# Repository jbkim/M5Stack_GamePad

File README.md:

# M5Stack_GamePad
### M5Stack용 Gamepad
- I2C 디바이스로 동작함
- M5Stack의 I2C포트에 연결이 되어 조이스틱의 값 및  버튼입력 값을 받을 수 있다.
- M5Stack용 Joystck과 사용법이 같다. https://docs.m5stack.com/#/en/unit/joystick
- 차이점은
    - requestFrom 함수의 인자값을 3 대신 4로 입력한다.
    - 키 버튼의 맵핑은 
    ```cpp
        void loop() {
        // put your main code here, to run repeatedly:
        Wire.requestFrom(JOY_ADDR, 4);
        if (Wire.available()) {
            x_data = Wire.read();
            y_data = Wire.read();
            select_data = Wire.read(); // Joystick button
            btn_data = Wire.read();    // Keypad button: up, down, left, right
                
            sprintf(data, "x:%d y:%d button:%d\n", x_data, y_data, select_data);
            Serial.print(data);

            if (btn_data & UP) Serial.println("UP");
            if (btn_data & DOWN) Serial.println("DOWN");
            if (btn_data & LEFT) Serial.println("LEFT");
            if (btn_data & RIGHT) Serial.println("RIGHT");                
        }
        delay(200);
        }
    ```

- History
    - Version 1.0

    - Version 1.1
        - I2C 포트의 위치 변경
        - 홀 사이즈 변경
        - PCB 레이아웃 변경

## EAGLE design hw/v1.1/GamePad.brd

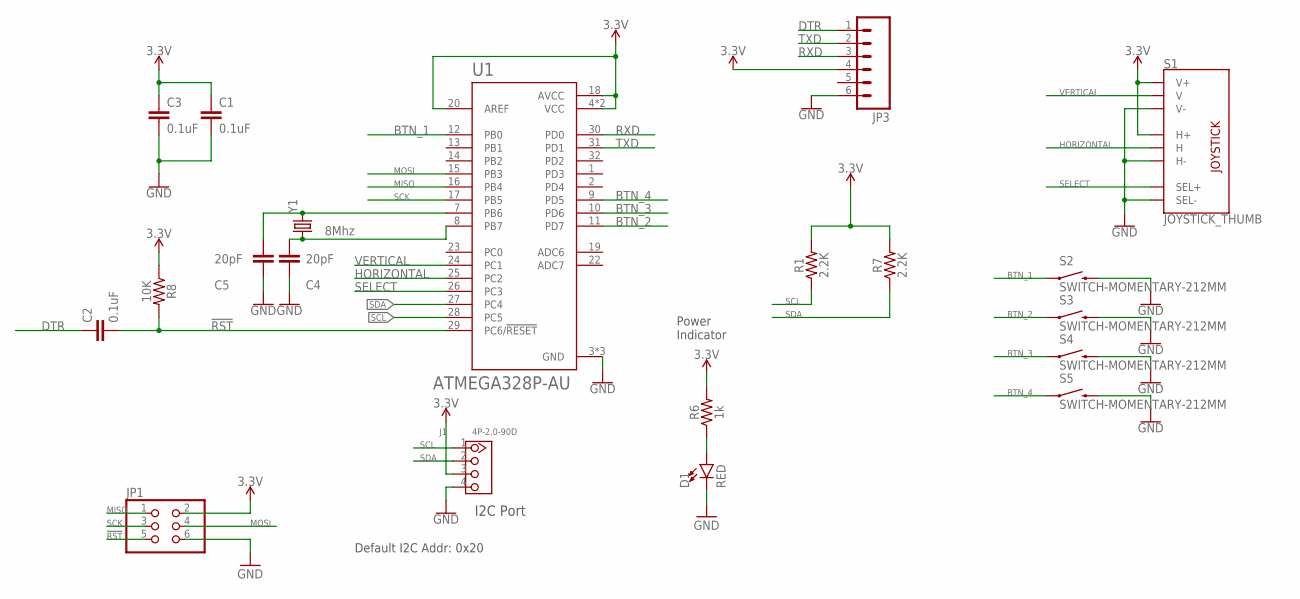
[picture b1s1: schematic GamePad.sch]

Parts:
C1, C2, C3: 0.1uF; 0603-CAP
C4, C5: 20pF; 0603-CAP
D1: RED; LED-0603
J1: 4P-2.0-90D; HW4-2.0-90D
JP1: PINHD-2X3; 2X03
JP3: M06LOCK; 1X06_LOCK
R1, R7: 2.2K; 0603
R6: 1k; 0603
R8: 10K; 0603
S1: JOYSTICK_THUMB; JOYSTICK
S2, S3, S4, S5: SWITCH-MOMENTARY-212MM; TACTILE-PTH-12MM
U1: ATMEGA328P-AU; QFP80P900X900X120-32N
Y1: 8Mhz; HC49UP

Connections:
3.3V: C1.1, C3.1, J1.3, JP1.2, JP3.4, R1.2, R6.2, R7.2, R8.1, S1.H1 (H+), S1.V1 (V+), U1.4 (VCC), U1.6 (VCC), U1.18 (AVCC), U1.20 (AREF)
!RST: C2.2, JP1.5, R8.2, U1.29 (PC6/!RESET)
BTN_1: S2.1, U1.12 (PB0)
BTN_2: S3.1, U1.11 (PD7)
BTN_3: S4.1, U1.10 (PD6)
BTN_4: S5.1, U1.9 (PD5)
DTR: C2.1, JP3.1
GND: C1.2, C3.2, C4.1, C5.1, D1.C, J1.4, JP1.6, JP3.6, S1.B2A (SEL-), S1.H3 (H-), S1.V3 (V-), S2.3 (2), S3.3 (2), S4.3 (2), S5.3 (2), U1.3 (GND), U1.5 (GND), U1.21 (GND)
HORIZONTAL: S1.H2 (H), U1.25 (PC2)
MISO: JP1.1, U1.16 (PB4)
MOSI: JP1.4, U1.15 (PB3)
unnamed: D1.A, R6.1
unnamed: C5.2, U1.7 (PB6), Y1.2
unnamed: C4.2, U1.8 (PB7), Y1.1
RXD: JP3.3, U1.30 (PD0)
SCK: JP1.3, U1.17 (PB5)
SCL: J1.1, R1.1, U1.28 (PC5)
SDA: J1.2, R7.1, U1.27 (PC4)
SELECT: S1.B1A (SEL+), U1.26 (PC3)
TXD: JP3.2, U1.31 (PD1)
VERTICAL: S1.V2 (V), U1.24 (PC1)

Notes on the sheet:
Power Indicator
I2C Port
Default I2C Addr: 0x20

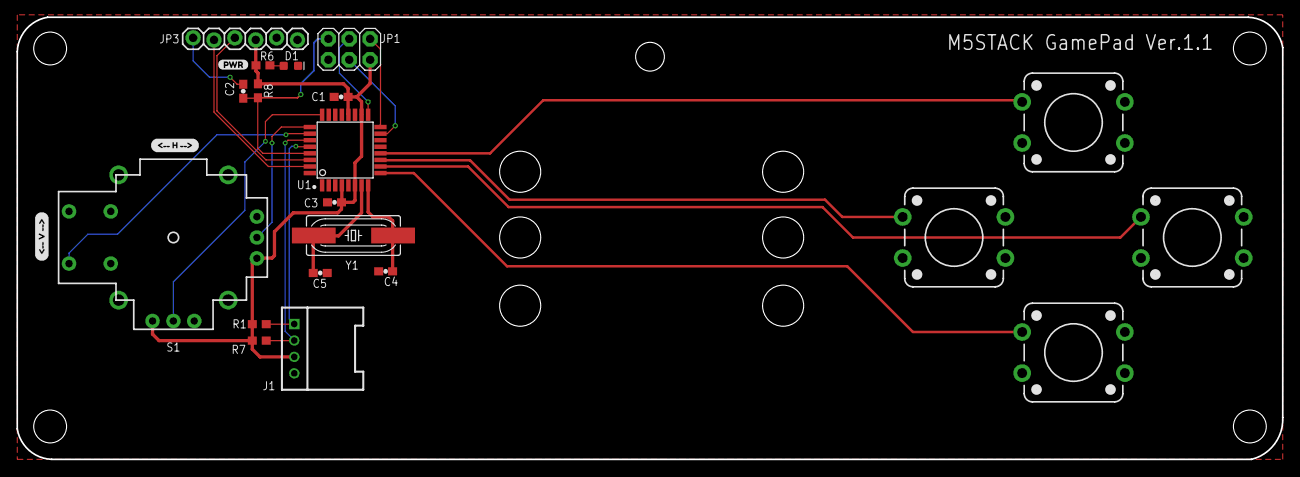
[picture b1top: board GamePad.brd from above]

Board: 2 copper layers, 154.0 x 53.8 mm, 23 parts (0 on the bottom side), 21 nets.

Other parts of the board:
U$7: ###_V_###0
U$14: PWR-()-03
U$15: ###_H_###1

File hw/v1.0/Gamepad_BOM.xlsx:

| GamePad BOM |  |  |  |  | 43514
 | Parts Reference | Value | Device | Package | Qty | Description
1 | JP2 |  | Pin header 2.54 pitch | 1X04 | 1
2 | JP1 |  | Pin header 2.54 pitch | 2X03 | 1
3 | C1, C3 | 0.1uF | Chip Capacitor (16V, J급) | 1608 | 2
4 | R8 | 10K | Chip Resistor (J급) | 1608 | 1
5 | R6 | 1k | Chip Resistor (J급) | 1608 | 1
6 | R1, R7 | 2.2K | Chip Resistor (J급) | 1608 | 2
7 | C4, C5 | 20pF | Chip Capacitor (16V, J급) | 1608 | 2
8 | Y1 | 3.6864Mhz (20pF) | Crystal SMD | HC49UP | 1 | http://www.devicemart.co.kr/goods/view?no=5267
9 | J1 | 4P-2.0-90D | Grove Connector | HW4-2.0-90D | 1 | https://www.digikey.com/product-detail/en/seeed-technology-c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
10 | U1 | ATMEGA328P-AU | ATMEGA328P-AU | TQFP32 | 1
11 | S1 |  | Analog JOYSTICK |  | 1 | http://www.icbanq.com/P006963674
12 | D1 | RED | Chip LED SMD | 1608 | 1
13 | S2, S3, S4, S5 | SWITCH-MOMENTARY-212MM | SWITCH-MOMENTARY-212MM | TACTILE-PTH-12MM | 4 | http://www.icbanq.com/P001429346

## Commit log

2019-04-08 upload hardware
2019-04-08 upload code
2019-04-09 update image

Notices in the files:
parts and their libraries:
SparkFun-Resistors: Licensing: Creative Commons ShareAlike 4.0 International - https://creativecommons.org/licenses/by-sa/4.0
